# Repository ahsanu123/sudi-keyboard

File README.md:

<p >

</p>

# 🌿 _Sudi_ V2

Sudi V2 is custom wireless split keyboard based on NRF52832 Nordic Semiconductor Microcontroller series, each side consist 18 keys 36 in totals, use MCP23017 I2C 
I/O expansion to scan one side of keyboard, and use wire to trasfer data to NRF52. Built in SWD debug port, with Serial Logger based on CH340G. Sudi Have interactive 
RGB LED and OLED 0.91 inch for graphic display. Planned to create 3D print enclosure.

## 💾 hardware 
hardware is designed with Kicad, you can find out hardware design in `pcb-design` folder. 

**Over simplified workflow**
```mermaid
flowchart TD
    MatrixScanner[Matrix Scanner]
    COR[Chain Of Responsibility]
    FinalReport
    HIDBLEServer[BLE HID Server]

    MatrixScanner --> COR
    COR --> FinalReport
    FinalReport --> HIDBLEServer
```

<details>
  <summary>Casing Design</summary>

</details>

## 🔥 Progress Log

<details>
  <summary>expand this to see current progress 🍰 </summary>

- ~~try to understand why linker script flash ram address need to change from `0x8000` to `0x4000` [look this thread](https://devzone.nordicsemi.com/f/nordic-q-a/78577/nrf-sdk-pre-built-blinky-hex-works-compiled-hex-does-not-nrf51822)~~, use Zephyr instead.
- ~~update hardware readme.md section, add schematic svg~~
- ~~try to logging with segger jlink rtt~~ at 9 september 2024 22:09
- try to logging with serial logger
- ~~add usb to serial (ch340g) if serial logger worked /or considering to use segger rtt (worked and tested on NRF51822)~~
- ~~add on off switch for board~~
- ~~🦀 Change design to use NRF52832~~
- 🔥 Learn more about Zephyr
- ~~change JTAG debugger to component with less space and same pinout based on JLink v8 pinout.~~
- 🔋 ~~battery/and its charger need adjustment, because NRF5232 power supply range is 1.7 V to 3.6 V , and TP4056 will shutdown on 4.2V. if you add AMS1117 3.3v to regulate it, AMS1117 need at least 4.5V to maintain its 3.3V.~~ (NAH, use buck boost instead)
- 🔋 read about BQ24075 bms datasheet
- 🔋 Read about  MAX17048  datasheet
- 🔋 ~~if we use 1.8V for NRF Voltage supply, how its affect other used component~~
  - 🪔 ~~WS2812 VIO level was not satisfied, based on its datasheet, min supply is 3.5, VIH 0.7*VDD (2.45), VIL 0.3 *VDD (1.05)~~
  - ⚗️ ~~based on MCP23017 datashet its power voltage range is 1.8V to 5.5v, VIH 0.25 VDD + 0.8, VIL 0.8 VDD, so its possible to use MCP23017 with 1.8V NRF voltage supply,~~
  - 🐤 ~~CH340G~~
- ~~🔶check 4 pin crystal compatibility~~
- 🦄 ~~change MCU to use NRF52833?? (power supply 1.7-5.5), usb, price +1 dollar 😥, or (NRF52820 only $2.6348)~~
- 🧀 ~~Recheck Silk Screen and componnent~~
- 💸 ~~Create Manufacture id BOM, and Order it~~ about 70 dollar
- 💸 ~~wait dollar until it lower, and order all needed component.~~ shit!!!, dollar does not decline
- ⚽ ~~Final Re-Inspection~~ not doing it actually
- 💸 ~~ordered pcb. 5 Pcs for $15.72 with shipment 7.02 dollar and the pcb is 8.7, still wait for tax. ⏰ 19 januari 2025 at 22:16,~~ arrived in 7 Februari
- 👘 Ordering Component 58 dollar free shipping ( shipping is 7 dollar) , ⏰ 8 Februari 2025
- 💼 Casing - Left Right Connector
- 💼 Casing - top fastener
- 💼 Casing - Battery Holder
- 28 April 2025 ⏰ 05:47, finish one side small component soldering, there is still a lot solder bridge, need to recheck before aplying power
- 🐞 **BUG**, 1 Mei 2025 ⏰17:29, cell pin need to connect into battery pin, not 3.3v

- 🐞 **BUG**, 9 Mei 2025 ⏰ 20:18 current version 2 gerber used for manufacturing pcb is not updated, there is shorted between 3.3v and gnd
- 🐞 **BUG**, 13 Mei 2025 ⏰ 06:52 look and re-calculate inductor 5v buck-boost, when its at full load (all ws28 12 is on) inductor is burn, but ic is not.

> change inductor to use power inductor like VLF4012-2R2 (2.2uH, 1.5A), or choose same capacitance with higher current rate.
>
> look this [lcsc power inductor](https://www.lcsc.com/product-detail/Power-Inductors_MetalLions-MTQH201608S2R2MBT_C17701122.html?s_z=n_VLF4012-2R2%2520)

- 🎰 able to run and flash RMK example with jlink and probe-rs ⏰ 9 Mei 2025, 20:19
- basic setup on WSL, so able to develop in WSL ⏰ 20 Mei 2025, 05:26

  to debugging you need bridge usb device from windows to wsl with `usbipd`

  ```shell
  C:\Windows\System32> usbipd list
  Connected:
  BUSID  VID:PID    DEVICE                                                        STATE
  1-1    feed:0ffa  USB Input Device                                              Not shared
  1-2    0000:3825  USB Input Device                                              Not shared
  1-4    0bda:0129  Realtek USB 2.0 Card Reader                                   Not shared
  1-5    13d3:56cb  USB2.0 HD IR UVC WebCam                                       Not shared
  1-6    1366:0101  J-Link driver                                                 Not shared
  1-10   8087:0026  Intel(R) Wireless Bluetooth(R)                                Not shared

  Persisted:
  GUID                                  DEVICE

  C:\Windows\System32> usbipd bind --busid 1-6

  C:\Windows\System32> usbipd attach --wsl --busid 1-6
  usbipd: info: Using WSL distribution 'Arch' to attach; the device will be available in all WSL 2 distributions.
  usbipd: info: Detected networking mode 'nat'.
  usbipd: info: Using IP address 172.27.144.1 to reach the host.

  C:\Windows\System32>
  ```

  then you can access the usb device as in linux

- 24 Mei 2025, trying to run trouble bas example, its give good sign, even 5v sepic is died for now -> https://github.com/embassy-rs/trouble/blob/main/examples/apps/src/ble_bas_peripheral.rs ⏰ 09:01 

- 25 Mei 2025, able to read uuid for battery level on trouble bas example, also create basic reading uuid with bleak python library, but its really intermitent, bluez is more robust, several note to use and connect bluez with device.

also flashed firmware is from trouble example, current v2 firmware is compiled but not running, 🪞 need to investigate it

```shell
$ bluetoothctl
hci0 new_settings: powered bondable ssp br/edr le secure-conn
Agent registered

[bluetoothctl]> connect FF:E4:05:1A:8F:FF
[bluetoothctl]> disconnect FF:E4:05:1A:8F:FF
[bluetoothctl]> menu gatt
[bluetoothctl]> list-attributes
[bluetoothctl]> select-attribute /org/bluez/hci0/dev_FF_E4_05_1A_8F_FF/service0020/char0021
[bluetoothctl]> read
[bluetoothctl]>
```

- 3 Juli 2025, reading more about trouble, here is `trouble-host-macro` documentation located https://docs.rs/trouble-host-macros/latest/trouble_host_macros/ , here are some note
  - Peripherals may use **GATT** (Generic Attribute Profile) to expose **services** and **characteristics**,
  - still many question about why linker cant linking ble exampl (stack is overflow) even though its identical with example
  - this error ` cannot move location counter backwards (from 3ffdeca8 to 3ffdc000` is because `embassy-executor` `task-arena-<size>` i am not sure why and what value its shouuld be. but without defining task arena its compiled but `panic` on runtime.
  - ok, i find out making `embassy-executor` have `embassy-executor = { version = "0.7.0", features = ["task-arena-size-8192"]}` will make it compiled 😙, need to learn what is that.

finally at ⏰ 21:46 its compiled and able to run, its discoverable with phone 

- 23 Agustus 2025, finally my first SUDI was broke (MCU) and I must finish SUDI v2 for working.
- 24 agustus 2025, basic bas for nrf is compiled and flashed, ⏰ 13:25 

  ⏰ 21:29, able to advertise device as bluetooth hid, but still cant establishing connection to keyboard,
  need to understand how HID keyboard is connected in USB and in BLE.

- 11 September 2025, after reading more about BLE spesification, to more understand what each endpoint / characteristic does in BLE HID, you need to:
  * read characteristic code from [bluetooth assigned number](http://bluetooth.com/wp-content/uploads/Files/Specification/HTML/Assigned_Numbers/out/en/Assigned_Numbers.pdf). for example look at `2a4a` from `hid_info` property in this struct (take from RMK github)
    ```rust
    #[gatt_service(uuid = service::HUMAN_INTERFACE_DEVICE)]
    pub(crate) struct HidService {
        #[characteristic(uuid = "2a4a", read, value = [0x01, 0x01, 0x00, 0x03])]
        pub(crate) hid_info: [u8; 4],
        #[characteristic(uuid = "2a4b", read, value = KeyboardReport::desc().try_into().expect("Failed to convert KeyboardReport to [u8; 67]"))]
        pub(crate) report_map: [u8; 67],
        #[characteristic(uuid = "2a4c", write_without_response)]
        pub(crate) hid_control_point: u8,
        #[characteristic(uuid = "2a4e", read, write_without_response, value = 1)]
        pub(crate) protocol_mode: u8,
        #[descriptor(uuid = "2908", read, value = [0u8, 1u8])]
        #[characteristic(uuid = "2a4d", read, notify)]
        pub(crate) input_keyboard: [u8; 8],
        #[descriptor(uuid = "2908", read, value = [0u8, 2u8])]
        #[characteristic(uuid = "2a4d", read, write, write_without_response)]
        pub(crate) output_keyboard: [u8; 1],
    }
    ```
  * search `2a4a` on BLE Assigned number you will find **HID Information**
    
  * from that information (HID Information), look at [HID over gatt profile](https://www.bluetooth.com/specifications/specs/hid-over-gatt-profile-1-0/)
    
  * it will give you basic information of what is **HID information** is
  * to understand more about what value should provided by your device, you can continue to [Device Class Definition for HID](https://www.usb.org/sites/default/files/hid1_11.pdf), and try to search keyword from _HID over gatt profile_ description, for example `bcountryCode`, search on _Device class definition for HID_ then you will find **HID Descriptor**
    
  * from that information you can conclude `value = [0x01, 0x01, 0x00, 0x03])]` is HID Descriptor, then
  * `0x01` is _bLength_
  * `0x01` is _bDescriptorType_
  * `0x00` is _bcdHID_
  * `0x03` is _bCountryCode_
</details>

## 💳 Reference 

- [RMK - Rust Keyboard Firmware](https://github.com/HaoboGu/rmk/tree/main)   
- [Buck Boost for 3.3v](https://www.eevblog.com/forum/projects/regulating-lipo-battery-to-3-3v/)

<sup>🔥 make it V2 - 19 juni 2024 10:49</sup>

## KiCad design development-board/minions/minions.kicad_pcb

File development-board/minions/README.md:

# Minions

[Assembly View](https://kicanvas.org/?github=https%3A%2F%2Fgithub.com%2Fahsanu123%2Fsudi-keyboard%2Ftree%2Fmain%2Fdevelopment-board%2Fminions)

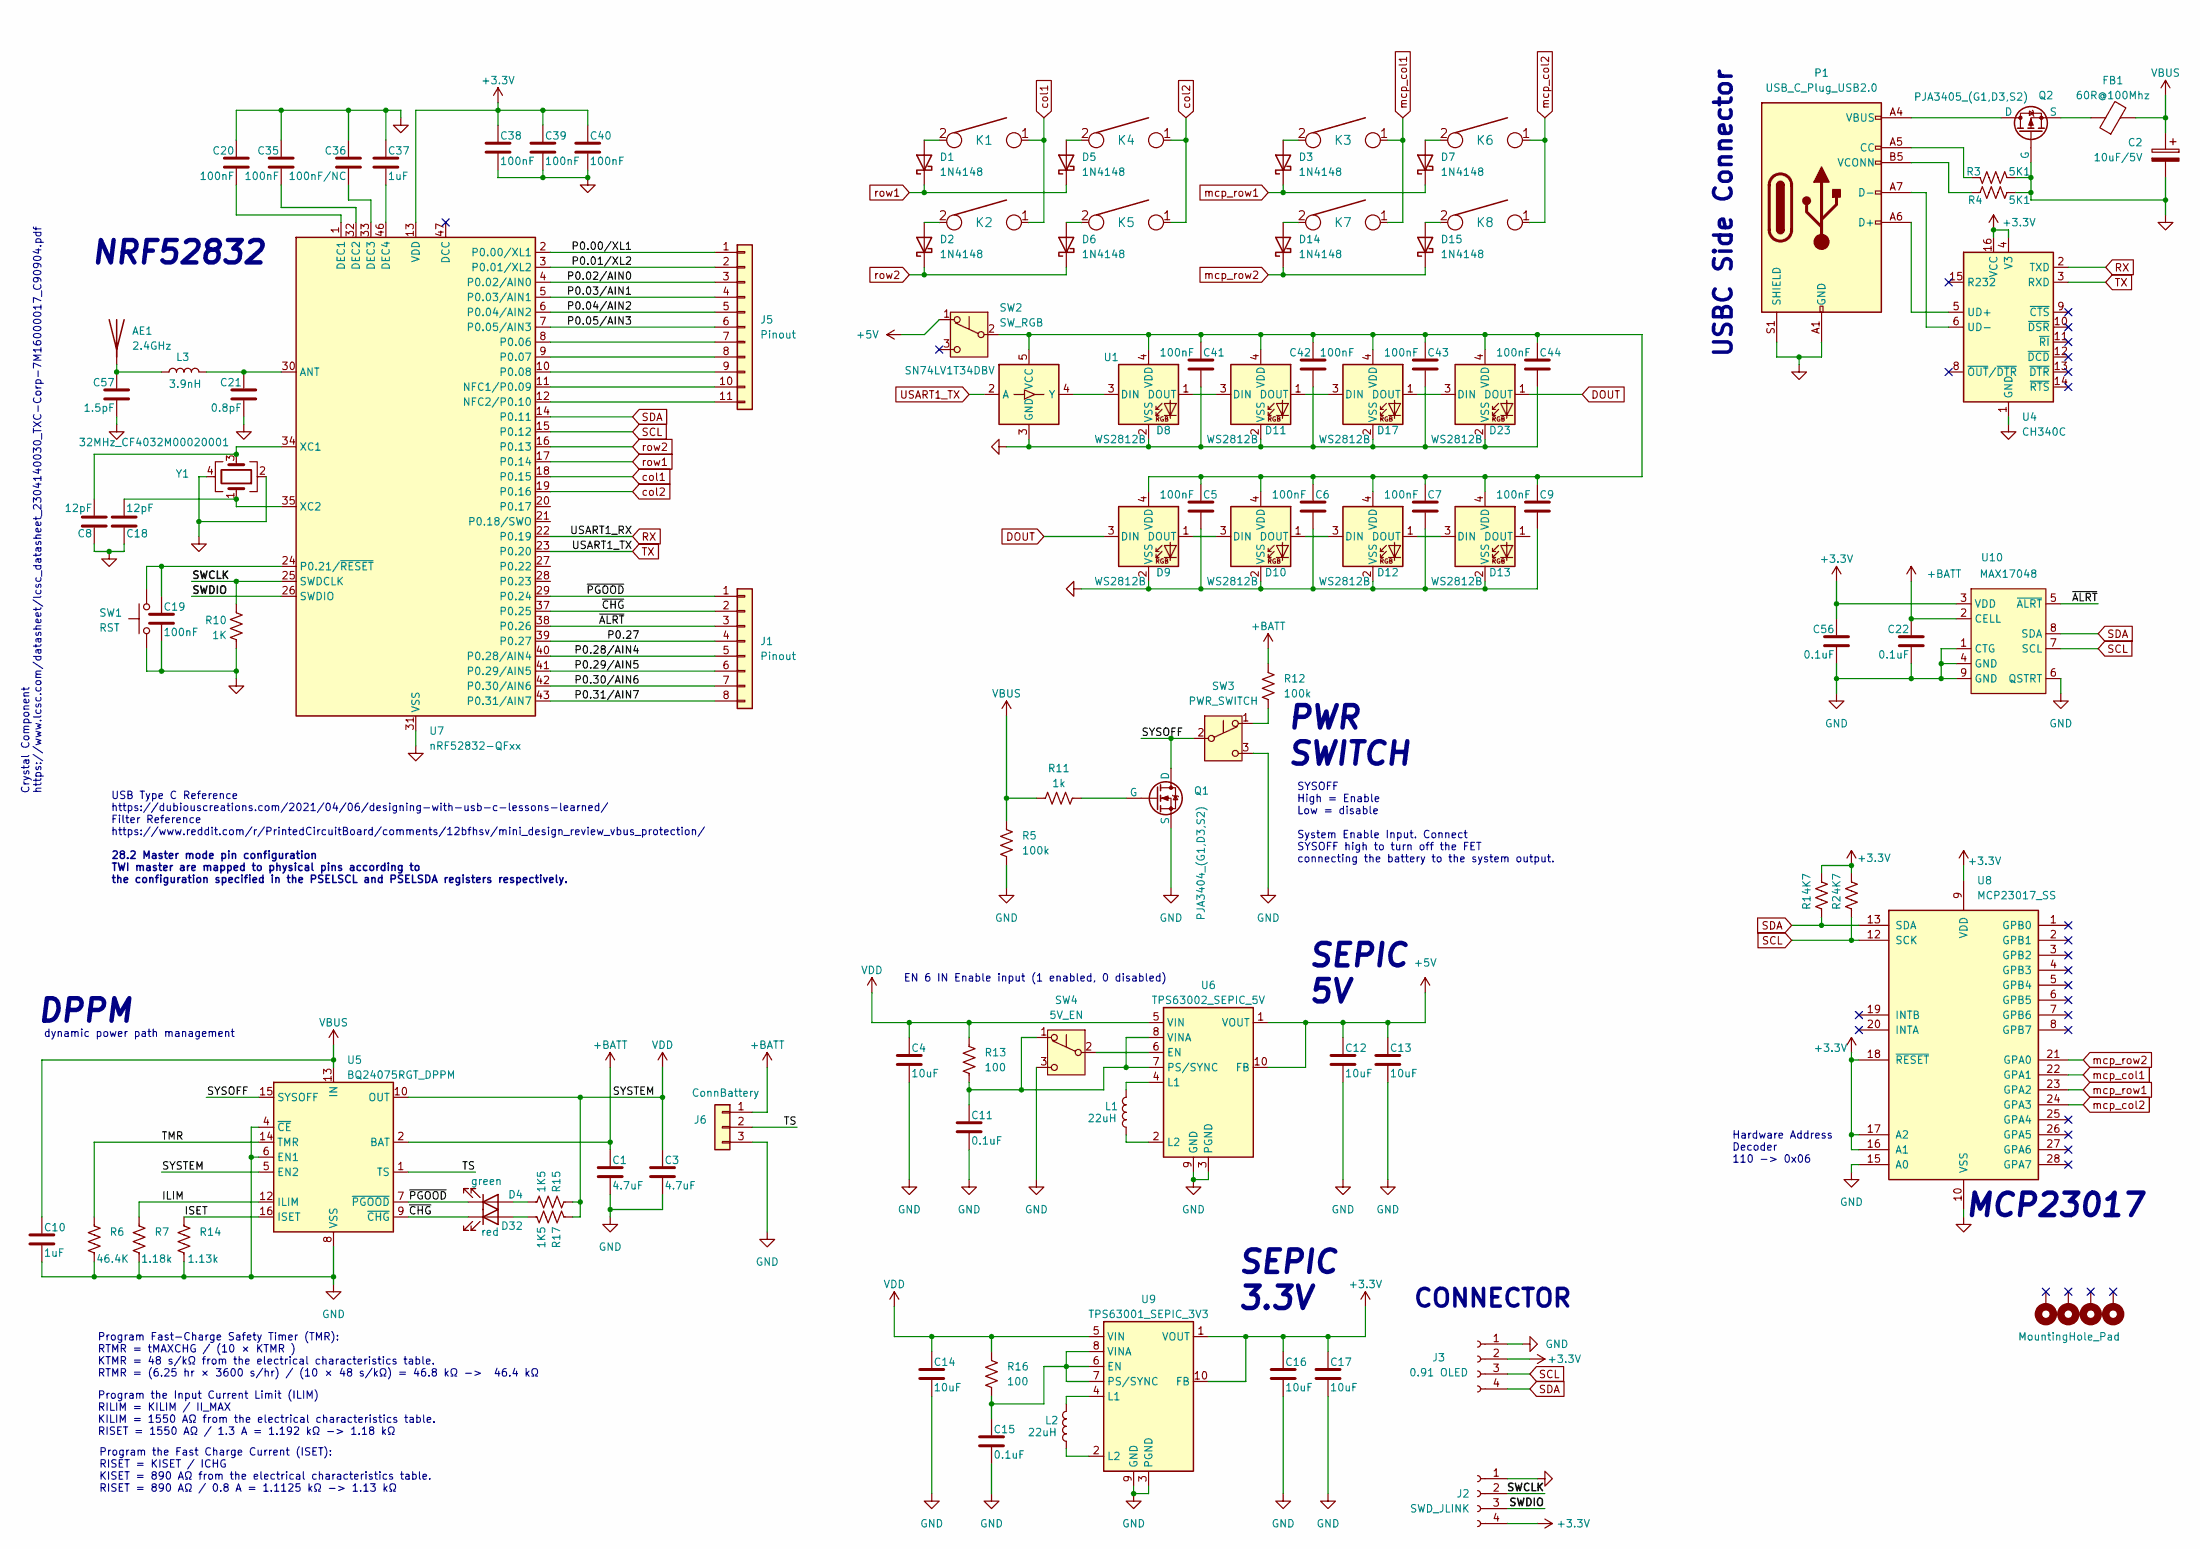
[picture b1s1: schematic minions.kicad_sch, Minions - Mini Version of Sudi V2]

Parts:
AE1: 2.4GHz; Texas_SWRA117D_2.4GHz_Left
C1, C3: 4.7uF; C_0805_2012Metric_Pad1.18x1.45mm_HandSolder
C2: 10uF/5V; C_0805_2012Metric_Pad1.18x1.45mm_HandSolder
C4, C12, C13, C14, C16, C17: 10uF; C_0805_2012Metric_Pad1.18x1.45mm_HandSolder
C5, C6, C7, C9, C19, C20, C35, C38, C39, C40, C41, C42, C43, C44: 100nF; C_0805_2012Metric_Pad1.18x1.45mm_HandSolder
C8, C18: 12pF; C_0805_2012Metric_Pad1.18x1.45mm_HandSolder
C10, C37: 1uF; C_0805_2012Metric_Pad1.18x1.45mm_HandSolder
C11, C15, C22, C56: 0.1uF; C_0805_2012Metric_Pad1.18x1.45mm_HandSolder
C21: 0.8pF; C_0805_2012Metric_Pad1.18x1.45mm_HandSolder
C36: 100nF/NC; C_0805_2012Metric_Pad1.18x1.45mm_HandSolder
C57: 1.5pF; C_0805_2012Metric_Pad1.18x1.45mm_HandSolder
D1, D2, D3, D5, D6, D7, D14, D15: 1N4148; D_SOD123_axial-dual
D4: green; LED_0805_2012Metric_Pad1.15x1.40mm_HandSolder
D8, D9, D10, D11, D12, D13, D17, D23: WS2812B; LED_WS2812B-2020_PLCC4_2.0x2.0mm
D32: red; LED_0805_2012Metric_Pad1.15x1.40mm_HandSolder
FB1: 60R@100Mhz; L_0603_1608Metric_Pad1.05x0.95mm_HandSolder
H4, H5, H6, H7: MountingHole_Pad; MountingHole_3.2mm_M3_DIN965_Pad
J1: Pinout; PinHeader_1x08_P2.54mm_Vertical
J2: SWD_JLINK; PinHeader_1x04_P2.54mm_Vertical
J3: 0.91 OLED; PinHeader_1x04_P2.54mm_Vertical
J5: Pinout; PinHeader_1x11_P2.54mm_Vertical
J6: ConnBattery; PinHeader_1x03_P2.54mm_Vertical
K1, K2, K3, K4, K5, K6, K7, K8: KEYSW; Kailh_socket_MX_optional_reversible_platemount
L1, L2: 22uH; L_Bourns_SRP7028A_7.3x6.6mm
L3: 3.9nH; L_0603_1608Metric_Pad1.05x0.95mm_HandSolder
P1: USB_C_Plug_USB2.0; USB_C_Receptacle_GCT_USB4110
Q1: PJA3404_(G1,D3,S2); SOT-23
Q2: PJA3405_(G1,D3,S2); SOT-23
R1, R2: 4K7; R_0805_2012Metric_Pad1.20x1.40mm_HandSolder
R3, R4: 5K1; R_0805_2012Metric_Pad1.20x1.40mm_HandSolder
R5, R12: 100k; R_0805_2012Metric_Pad1.20x1.40mm_HandSolder
R6: 46.4K; R_0805_2012Metric_Pad1.20x1.40mm_HandSolder
R7: 1.18k; R_0805_2012Metric_Pad1.20x1.40mm_HandSolder
R10: 1K; R_0805_2012Metric_Pad1.20x1.40mm_HandSolder
R11: 1k; R_0805_2012Metric_Pad1.20x1.40mm_HandSolder
R13, R16: 100; R_0805_2012Metric_Pad1.20x1.40mm_HandSolder
R14: 1.13k; R_0805_2012Metric_Pad1.20x1.40mm_HandSolder
R15, R17: 1K5; R_0805_2012Metric_Pad1.20x1.40mm_HandSolder
SW1: RST; SW_Push_1P1T_NO_6x6mm_H9.5mm
SW2: SW_RGB; SW_SPDT_PCM12
SW3: PWR_SWITCH; SW_SPDT_PCM12
SW4: 5V_EN; SW_SPDT_PCM12
U1: SN74LV1T34DBV; SOT-23-5_HandSoldering
U4: CH340C; SOIC-16_3.9x9.9mm_P1.27mm
U5: BQ24075RGT_DPPM; VQFN-16-1EP_3x3mm_P0.5mm_EP1.6x1.6mm
U6: TPS63002_SEPIC_5V; Texas_DRC0010J_ThermalVias
U7: nRF52832-QFxx; QFN-48-1EP_6x6mm_P0.4mm_EP4.6x4.6mm
U8: MCP23017_SS; SSOP-28_5.3x10.2mm_P0.65mm
U9: TPS63001_SEPIC_3V3; Texas_DRC0010J_ThermalVias
U10: MAX17048; DFN-8-1EP_2x2mm_P0.5mm_EP0.8x1.6mm
Y1: 32MHz_CF4032M00020001; Crystal_SMD_3225-4Pin_3.2x2.5mm_HandSoldering

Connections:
+3.3V: C16.1, C17.1, C38.1, C39.1, C40.1, C56.1, J2.4, J3.2, R1.1, R2.1, U4.4 (V3), U4.16 (VCC), U7.13 (VDD), U7.36 (VDD), U7.48 (VDD), U8.9 (VDD), U8.16 (A1), U8.17 (A2), U8.18 (~RESET), U9.1 (VOUT), U9.10 (FB), U10.3 (VDD)
+5V: C12.1, C13.1, SW2.1 (A), U6.1 (VOUT), U6.10 (FB)
+BATT: C1.1, C22.1, J6.1, R12.1, U5.2 (BAT), U5.3 (BAT), U10.2 (CELL)
/ILIM: R7.1, U5.12 (ILIM)
/ISET: R14.1, U5.16 (ISET)
/P0.00/XL1: J5.1, U7.2 (P0.00/XL1)
/P0.01/XL2: J5.2, U7.3 (P0.01/XL2)
/P0.02/AIN0: J5.3, U7.4 (P0.02/AIN0)
/P0.03/AIN1: J5.4, U7.5 (P0.03/AIN1)
/P0.04/AIN2: J5.5, U7.6 (P0.04/AIN2)
/P0.05/AIN3: J5.6, U7.7 (P0.05/AIN3)
/P0.27: J1.4, U7.39 (P0.27)
/P0.28/AIN4: J1.5, U7.40 (P0.28/AIN4)
/P0.29/AIN5: J1.6, U7.41 (P0.29/AIN5)
/P0.30/AIN6: J1.7, U7.42 (P0.30/AIN6)
/P0.31/AIN7: J1.8, U7.43 (P0.31/AIN7)
/SWCLK: J2.2, R10.2, U7.25 (SWDCLK)
/SWDIO: J2.3, U7.26 (SWDIO)
/SYSOFF: Q1.3 (D), SW3.2 (B), U5.15 (SYSOFF)
/TMR: R6.1, U5.14 (TMR)
/TS: J6.2, U5.1 (TS)
/~ALRT: J1.3, U7.38 (P0.26), U10.5 (~ALRT)
/~CHG: D32.1 (K), J1.2, U5.9 (~CHG), U7.37 (P0.25)
/~PGOOD: D4.1 (K), J1.1, U5.7 (~PGOOD), U7.29 (P0.24)
DOUT: D9.3 (DIN), D23.1 (DOUT)
GND: C1.2, C2.2, C3.2, C4.2, C5.2, C6.2, C7.2, C8.1, C9.2, C10.2, C11.2, C12.2, C13.2, C14.2, C15.2, C16.2, C17.2, C18.1, C19.2, C20.1, C21.2, C22.2, C35.1, C36.1, C37.1, C38.2, C39.2, C40.2, C41.2, C42.2, C43.2, C44.2, C56.2, C57.2, D8.2 (VSS), D9.2 (VSS), D10.2 (VSS), D11.2 (VSS), D12.2 (VSS), D13.2 (VSS), D17.2 (VSS), D23.2 (VSS), J2.1, J3.1, J6.3, P1.A1 (GND), P1.A12 (GND), P1.B1 (GND), P1.B12 (GND), P1.S1 (SHIELD), Q1.2 (S), Q2.1 (G), R3.2, R4.2, R5.2, R6.2, R7.2, R10.1, R14.2, SW1.1, SW3.3 (C), SW4.3 (C), U1.3 (GND), U4.1 (GND), U5.4 (~CE), U5.6 (EN1), U5.8 (VSS), U5.17 (VSS), U6.3 (PGND), U6.9 (GND), U6.11 (PGND), U7.31 (VSS), U7.45 (VSS), U7.49 (VSS), U8.10 (VSS), U8.15 (A0), U9.3 (PGND), U9.9 (GND), U9.11 (PGND), U10.1 (CTG), U10.4 (GND), U10.6 (QSTRT), U10.9 (GND), Y1.2, Y1.4
unnamed: AE1.1 (A), C57.1, L3.1
unnamed: D1.2 (A), K1.2
unnamed: D2.2 (A), K2.2
unnamed: D3.2 (A), K3.2
unnamed: D4.2 (A), R15.1
unnamed: D5.2 (A), K4.2
unnamed: D6.2 (A), K5.2
unnamed: D7.2 (A), K6.2
unnamed: D8.3 (DIN), U1.4 (Y)
unnamed: D9.1 (DOUT), D10.3 (DIN)
unnamed: D10.1 (DOUT), D12.3 (DIN)
unnamed: C5.1, C6.1, C7.1, C9.1, C41.1, C42.1, C43.1, C44.1, D8.4 (VDD), D9.4 (VDD), D10.4 (VDD), D11.4 (VDD), D12.4 (VDD), D13.4 (VDD), D17.4 (VDD), D23.4 (VDD), SW2.2 (B), U1.5 (VCC)
unnamed: D8.1 (DOUT), D11.3 (DIN)
unnamed: D11.1 (DOUT), D17.3 (DIN)
unnamed: D12.1 (DOUT), D13.3 (DIN)
unnamed: D14.2 (A), K7.2
unnamed: D15.2 (A), K8.2
unnamed: D17.1 (DOUT), D23.3 (DIN)
unnamed: D32.2 (A), R17.1
unnamed: J5.7, U7.8 (P0.06)
unnamed: J5.8, U7.9 (P0.07)
unnamed: J5.9, U7.10 (P0.08)
unnamed: J5.10, U7.11 (NFC1/P0.09)
unnamed: J5.11, U7.12 (NFC2/P0.10)
unnamed: P1.A5 (CC), R3.1
unnamed: P1.A6 (D+), U4.5 (UD+)
unnamed: P1.A7 (D-), U4.6 (UD-)
unnamed: P1.B5 (VCONN), R4.1
unnamed: Q1.1 (G), R11.2
unnamed: P1.A4 (VBUS), P1.A9 (VBUS), P1.B4 (VBUS), P1.B9 (VBUS), Q2.3 (D)
unnamed: FB1.1, Q2.2 (S)
unnamed: R12.2, SW3.1 (A)
unnamed: C11.1, R13.2, SW4.1 (A), U6.7 (PS/SYNC), U6.8 (VINA)
unnamed: SW4.2 (B), U6.6 (EN)
unnamed: L1.2, U6.4 (L1)
unnamed: L1.1, U6.2 (L2)
unnamed: C21.1, L3.2, U7.30 (ANT)
unnamed: C20.2, U7.1 (DEC1)
unnamed: C35.2, U7.32 (DEC2)
unnamed: C36.2, U7.33 (DEC3)
unnamed: C37.2, U7.46 (DEC4)
unnamed: C19.1, SW1.2, U7.24 (P0.21/~RESET)
unnamed: C8.2, U7.34 (XC1), Y1.3
unnamed: C18.2, U7.35 (XC2), Y1.1
unnamed: C15.1, R16.2, U9.6 (EN), U9.7 (PS/SYNC), U9.8 (VINA)
unnamed: L2.2, U9.4 (L1)
unnamed: L2.1, U9.2 (L2)
RX: U4.2 (TXD), U7.22 (P0.19)
SCL: J3.3, R2.2, U7.15 (P0.12), U8.12 (SCK), U10.7 (SCL)
SDA: J3.4, R1.2, U7.14 (P0.11), U8.13 (SDA), U10.8 (SDA)
TX: U1.2 (A), U4.3 (RXD), U7.23 (P0.20)
VBUS: C2.1, C10.1, FB1.2, R5.1, R11.1, U5.13 (IN)
VDD: C3.1, C4.1, C14.1, R13.1, R15.2, R16.1, R17.2, U5.5 (EN2), U5.10 (OUT), U5.11 (OUT), U6.5 (VIN), U9.5 (VIN)
col1: K1.1, K2.1, U7.18 (P0.15)
col2: K4.1, K5.1, U7.19 (P0.16)
mcp_col1: K3.1, K7.1, U8.22 (GPA1)
mcp_col2: K6.1, K8.1, U8.24 (GPA3)
mcp_row1: D3.1 (K), D7.1 (K), U8.23 (GPA2)
mcp_row2: D14.1 (K), D15.1 (K), U8.21 (GPA0)
row1: D1.1 (K), D5.1 (K), U7.17 (P0.14)
row2: D2.1 (K), D6.1 (K), U7.16 (P0.13)

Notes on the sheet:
DPPM
EN 6 IN Enable input (1 enabled, 0 disabled)
dynamic power path management
28.2 Master mode pin configuration TWI master are mapped to physical pins according to the configuration specified in the PSELSCL and PSELSDA registers respectively.
SEPIC 5V
USB Type C Reference https://dubiouscreations.com/2021/04/06/designing-with-usb-c-lessons-learned/ Filter Reference https://www.reddit.com/r/PrintedCircuitBoard/comments/12bfhsv/mini_design_review_vbus_protection/
Program the Input Current Limit (ILIM) RILIM = KILIM / II_MAX KILIM = 1550 AΩ from the electrical characteristics table. RISET = 1550 AΩ / 1.3 A = 1.192 kΩ -> 1.18 kΩ
USBC Side Connector
NRF52832
MCP23017
PWR SWITCH
SEPIC 3.3V
Crystal Component https://www.lcsc.com/datasheet/lcsc_datasheet_2304140030_TXC-Corp-7M16000017_C90904.pdf
Program the Fast Charge Current (ISET): RISET = KISET / ICHG KISET = 890 AΩ from the electrical characteristics table. RISET = 890 AΩ / 0.8 A = 1.1125 kΩ -> 1.13 kΩ
CONNECTOR
Hardware Address Decoder 110 -> 0x06
Program Fast-Charge Safety Timer (TMR): RTMR = tMAXCHG / (10 × KTMR ) KTMR = 48 s/kΩ from the electrical characteristics table. RTMR = (6.25 hr × 3600 s/hr) / (10 × 48 s/kΩ) = 46.8 kΩ -> 46.4 kΩ
SYSOFF High = Enable Low = disable System Enable Input. Connect SYSOFF high to turn off the FET connecting the battery to the system output.

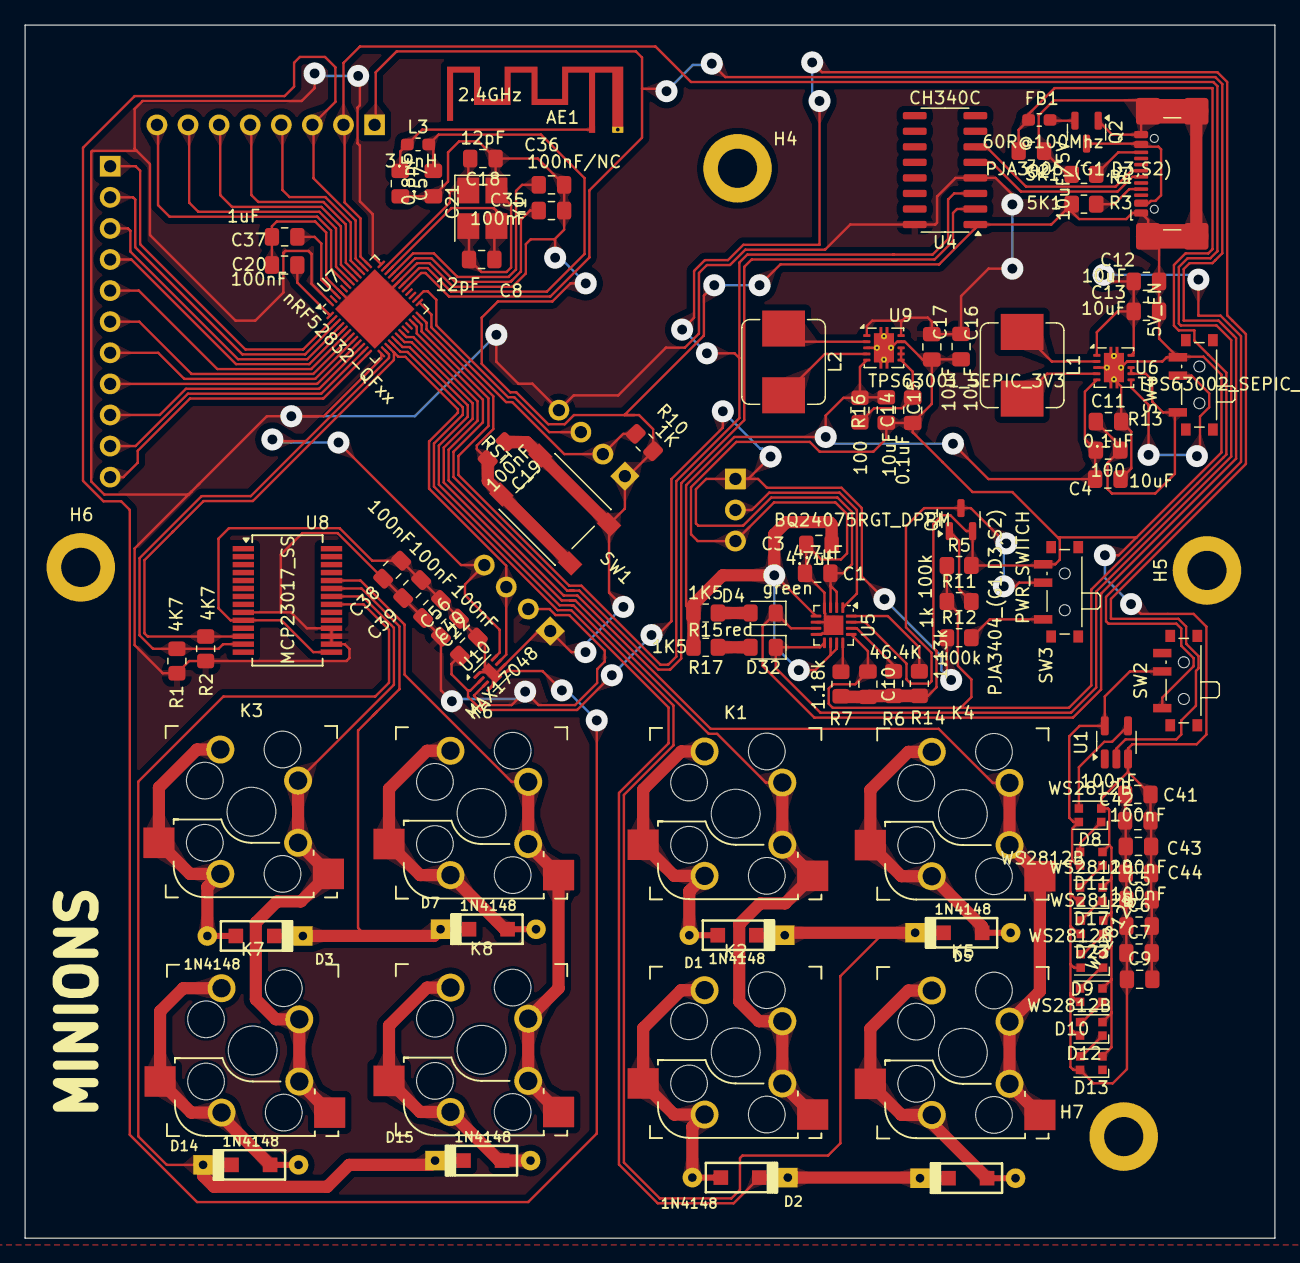
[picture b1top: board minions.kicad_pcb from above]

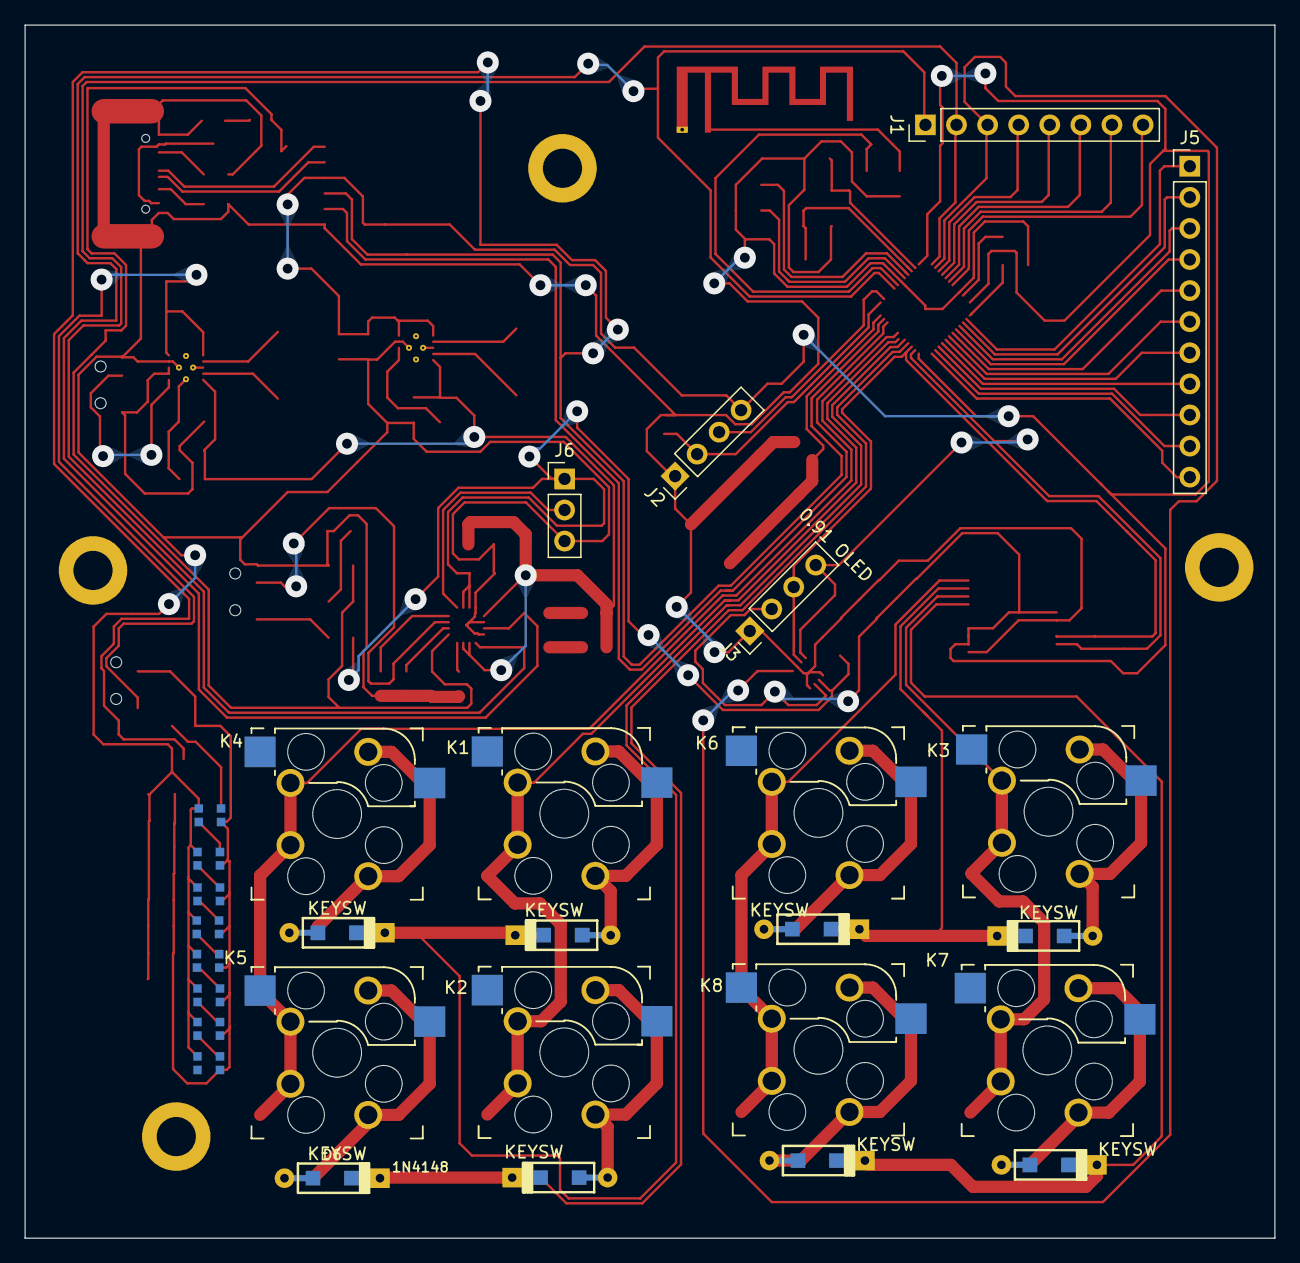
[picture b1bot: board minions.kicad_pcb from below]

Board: 2 copper layers, 102.1 x 99.1 mm, 105 parts (14 on the bottom side), 87 nets.

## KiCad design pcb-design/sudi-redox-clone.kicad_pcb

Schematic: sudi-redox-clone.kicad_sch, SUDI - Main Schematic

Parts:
AE1: 2.4GHz; Texas_SWRA117D_2.4GHz_Left
C1, C4: 10uF; C_0805_2012Metric_Pad1.18x1.45mm_HandSolder
C2, C3: 10uF/5V; C_0805_2012Metric_Pad1.18x1.45mm_HandSolder
C11, C13, C21: 100nF; C_0805_2012Metric_Pad1.18x1.45mm_HandSolder
C12: 47nF; C_0805_2012Metric_Pad1.18x1.45mm_HandSolder
C14: 1nF; C_0805_2012Metric_Pad1.18x1.45mm_HandSolder
C15: 2.2pF; C_0805_2012Metric_Pad1.18x1.45mm_HandSolder
C16: 1pF; C_0805_2012Metric_Pad1.18x1.45mm_HandSolder
C17: 1.5p; C_0805_2012Metric_Pad1.18x1.45mm_HandSolder
C18: 2.2nF; C_0805_2012Metric_Pad1.18x1.45mm_HandSolder
C19, C20: 12pF; C_0805_2012Metric_Pad1.18x1.45mm_HandSolder
D1, D2, D3, D7, D8, D9, D13, D14, D15, D19, D20, D21, D25, D26, D27, D29, D30, D31: 1N5820; D_SOD123_axial-dual
D4: RED; LED_0805_2012Metric_Pad1.15x1.40mm_HandSolder
D5, D6, D10, D11, D12, D16, D17, D18, D22, D23, D24, D28, D43, D44, D45, D46, D47, D48: WS2812B; LED_WS2812B_PLCC4_5.0x5.0mm_P3.2mm
FB1: 60R@100Mhz; L_0603_1608Metric_Pad1.05x0.95mm_HandSolder
FID1, FID2, FID3, FID4, FID5, FID6, FID7, FID8, FID9: Fiducial; Fiducial_1mm_Mask3mm
H1, H2, H3, H4, H5, H6, H7, H8, H9: MountingHole_Pad; MountingHole_3.2mm_M3_DIN965_Pad
J1: RJ12_LEFT; RJ25_Wayconn_MJEA-660X1_Horizontal
J2: 0.91 OLED; PinHeader_1x04_P2.54mm_Vertical
J3: RJ12_RIGHT; RJ25_Wayconn_MJEA-660X1_Horizontal
J4: USBC_PWR_ONLY; USB_C_Receptacle_GCT_USB4125-xx-x-0190_6P_TopMnt_Horizontal
J7: ARMJTAG; PinHeader_2x05_P2.54mm_Horizontal
J8: BatCon; PinHeader_1x02_P2.54mm_Horizontal
K1, K2, K3, K4, K5, K6, K7, K8, K9, K10, K11, K12, K13, K14, K15, K16, K17, K18: KEYSW; Mx_Alps_100-dualside
L1: 10nH; L_0603_1608Metric_Pad1.05x0.95mm_HandSolder
L2: 4.7nH; L_0603_1608Metric_Pad1.05x0.95mm_HandSolder
L3: 3.3nH; L_0603_1608Metric_Pad1.05x0.95mm_HandSolder
R1, R2: 4K7; R_1206_3216Metric
R3, R4: 5K1; R_1206_3216Metric
R5, R6: 1K; R_1206_3216Metric
R7: 1.2; R_1206_3216Metric
U4: AMS1117-3.3; SOT-223-3_TabPin2
U5: nRF51x22-QFxx; QFN-48-1EP_6x6mm_P0.4mm_EP4.6x4.6mm
U6: TP4056; SOIC-8-1EP_3.9x4.9mm_P1.27mm_EP2.29x3mm
U8: MCP23017_SS; SSOP-28_5.3x10.2mm_P0.65mm
Y2: 16MHz; Crystal_HC50_Vertical

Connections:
+3.3V: C3.1, C13.1, C14.1, C21.1, J7.1 (VTref), R1.1, R2.1, U4.2 (VO), U5.1 (VDD), U5.12 (VDD), U5.35 (AVDD), U5.36 (AVDD), U8.9 (VDD); also elsewhere on the board
+3V7: D5.1 (VDD), D6.1 (VDD), D10.1 (VDD), D11.1 (VDD), D12.1 (VDD), D16.1 (VDD), D17.1 (VDD), D18.1 (VDD), D22.1 (VDD), D23.1 (VDD), D24.1 (VDD), D28.1 (VDD), D43.1 (VDD), D44.1 (VDD), D45.1 (VDD), D46.1 (VDD), D47.1 (VDD), D48.1 (VDD), J1.5, J2.2, J3.5
+5V: C1.1, C2.1, D4.2 (A), FB1.2, J1.6, J3.6, U4.3 (VI), U6.4 (VCC), U6.8 (CE), U8.16 (A1), U8.17 (A2), U8.18 (~RESET); also elsewhere on the board
/I2C2_SCL: U5.4 (P0.0)
/I2C2_SDA: U5.5 (P0.1)
/SWCLK: J7.4 (SWCLK/TCK), R5.2, U5.24 (SWDCLK)
/SWDIO: J7.2 (SWDIO/TMS), U5.23 (SWDIO/~RST)
/USART1_RX: U5.7 (P0.3)
/USART1_TX: D43.4 (DIN), U5.6 (P0.2)
GND: C1.2, C2.2, C3.2, C4.2, C11.2, C12.2, C13.2, C14.2, C16.2, C17.2, C18.2, C19.1, C20.1, C21.2, D5.3 (VSS), D6.3 (VSS), D10.3 (VSS), D11.3 (VSS), D12.3 (VSS), D16.3 (VSS), D17.3 (VSS), D18.3 (VSS), D22.3 (VSS), D23.3 (VSS), D24.3 (VSS), D28.3 (VSS), D43.3 (VSS), D44.3 (VSS), D45.3 (VSS), D46.3 (VSS), D47.3 (VSS), D48.3 (VSS), H8.1, H9.1, J1.1, J2.1, J3.1, J4.A12 (GND), J4.B12 (GND), J4.S1 (SHIELD), J7.3 (GND), J7.5 (GND), J7.9 (GNDDetect), J8.2, R3.2, R4.2, R5.1, R7.1, U4.1 (GND), U5.13 (VSS), U5.33 (VSS), U5.34 (VSS), U5.49 (EP), U6.3 (GND), U8.10 (VSS), U8.15 (A0); also elsewhere on the board
unnamed: AE1.1 (A), C17.1, L3.1
unnamed: C15.2, C16.1, L3.2
unnamed: D1.2 (A), K1.2
unnamed: D2.2 (A), K2.2
unnamed: D3.2 (A), K3.2
unnamed: D4.1 (K), R6.2
unnamed: D5.2 (DOUT), D6.4 (DIN)
unnamed: D7.2 (A), K4.2
unnamed: D8.2 (A), K5.2
unnamed: D9.2 (A), K6.2
unnamed: D6.2 (DOUT), D10.4 (DIN)
unnamed: D10.2 (DOUT), D11.4 (DIN)
unnamed: D11.2 (DOUT), D12.4 (DIN)
unnamed: D12.2 (DOUT), D16.4 (DIN)
unnamed: D13.2 (A), K7.2
unnamed: D14.2 (A), K8.2
unnamed: D15.2 (A), K9.2
unnamed: D16.2 (DOUT), D17.4 (DIN)
unnamed: D17.2 (DOUT), D18.4 (DIN)
unnamed: D18.2 (DOUT), D22.4 (DIN)
unnamed: D19.2 (A), K10.2
unnamed: D20.2 (A), K11.2
unnamed: D21.2 (A), K12.2
unnamed: D22.2 (DOUT), D23.4 (DIN)
unnamed: D23.2 (DOUT), D24.4 (DIN)
unnamed: D24.2 (DOUT), D28.4 (DIN)
unnamed: D25.2 (A), K13.2
unnamed: D26.2 (A), K14.2
unnamed: D27.2 (A), K15.2
unnamed: D29.2 (A), K16.2
unnamed: D30.2 (A), K17.2
unnamed: D31.2 (A), K18.2
unnamed: D43.2 (DOUT), D44.4 (DIN)
unnamed: D44.2 (DOUT), D45.4 (DIN)
unnamed: D45.2 (DOUT), D46.4 (DIN)
unnamed: D46.2 (DOUT), D47.4 (DIN)
unnamed: D47.2 (DOUT), D48.4 (DIN)
unnamed: D5.4 (DIN), D48.2 (DOUT)
unnamed: FB1.1, J4.A9 (VBUS), J4.B9 (VBUS)
unnamed: J4.A5 (CC1), R3.1
unnamed: J4.B5 (CC2), R4.1
unnamed: C4.1, J8.1, U6.5 (BAT)
unnamed: L1.1, L2.2, U5.31 (ANT1)
unnamed: C15.1, L2.1, U5.32 (ANT2)
unnamed: C11.1, U5.39 (DEC1)
unnamed: C12.1, U5.29 (DEC2)
unnamed: C18.1, L1.2, U5.30 (VDD_PA)
unnamed: C19.2, U5.37 (XC1), Y2.1
unnamed: C20.2, U5.38 (XC2), Y2.2
unnamed: R7.2, U6.2 (PROG)
unnamed: R6.1, U6.7 (~CHRG)
SCL: J1.3, J2.3, J3.3, R2.2, U8.12 (SCK)
SDA: J1.4, J2.4, J3.4, R1.2, U8.13 (SDA)
Tx: J1.2, J3.2
col1: K1.1, K2.1, K3.1, U5.11 (P0.7), U8.1 (GPB0)
col2: K4.1, K5.1, K6.1, U5.14 (P0.8), U8.2 (GPB1)
col3: K7.1, K8.1, K9.1, U5.15 (P0.9), U8.3 (GPB2)
col4: K10.1, K11.1, K12.1, U5.16 (P0.10), U8.4 (GPB3)
col5: K13.1, K14.1, K15.1, U5.17 (P0.11), U8.5 (GPB4)
col6: K16.1, K17.1, K18.1, U5.18 (P0.12), U8.6 (GPB5)
row1: D1.1 (K), D7.1 (K), D13.1 (K), D19.1 (K), D25.1 (K), D29.1 (K), U5.8 (P0.4), U8.21 (GPA0)
row2: D2.1 (K), D8.1 (K), D14.1 (K), D20.1 (K), D26.1 (K), D30.1 (K), U5.9 (P0.5), U8.22 (GPA1)
row3: D3.1 (K), D9.1 (K), D15.1 (K), D21.1 (K), D27.1 (K), D31.1 (K), U5.10 (P0.6), U8.23 (GPA2)

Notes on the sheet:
SUDI - Split Keyboard SUDI is my custom split keyboard based on redox, it will designed with 75%+ keyboard layout (84 key with 42 each side). use promicro for main MCU and MCP23017 for 16bit bidirectional I/O expantion kailh hot swap
OLED 0.91'
28.2 Master mode pin configuration TWI master are mapped to physical pins according to the configuration specified in the PSELSCL and PSELSDA registers respectively.
V2 TODO make it wireless with NRF51822 add BMS to System (TP4056) make receiver and transmitter with NRF use LUFA with ATMega8 for usb receiver / RECEIVER SCH https://www.fourwalledcubicle.com/files/LUFA/Doc/120219/html/_page__a_v_r8_support.html https://developer.nordicsemi.com/nRF5_SDK/nRF51_SDK_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
NOTE: Used Real Diode 1N4148
Key Matrix
USB Type C Reference https://dubiouscreations.com/2021/04/06/designing-with-usb-c-lessons-learned/ Filter Reference https://www.reddit.com/r/PrintedCircuitBoard/comments/12bfhsv/mini_design_review_vbus_protection/
Hardware Address Decoder 110 -> 0x06
ADD USB B Backup
RJ12 Female Conn Change To Correct Footprint
Ref: Figure 24 NRF51822 Datasheet
MCP23017

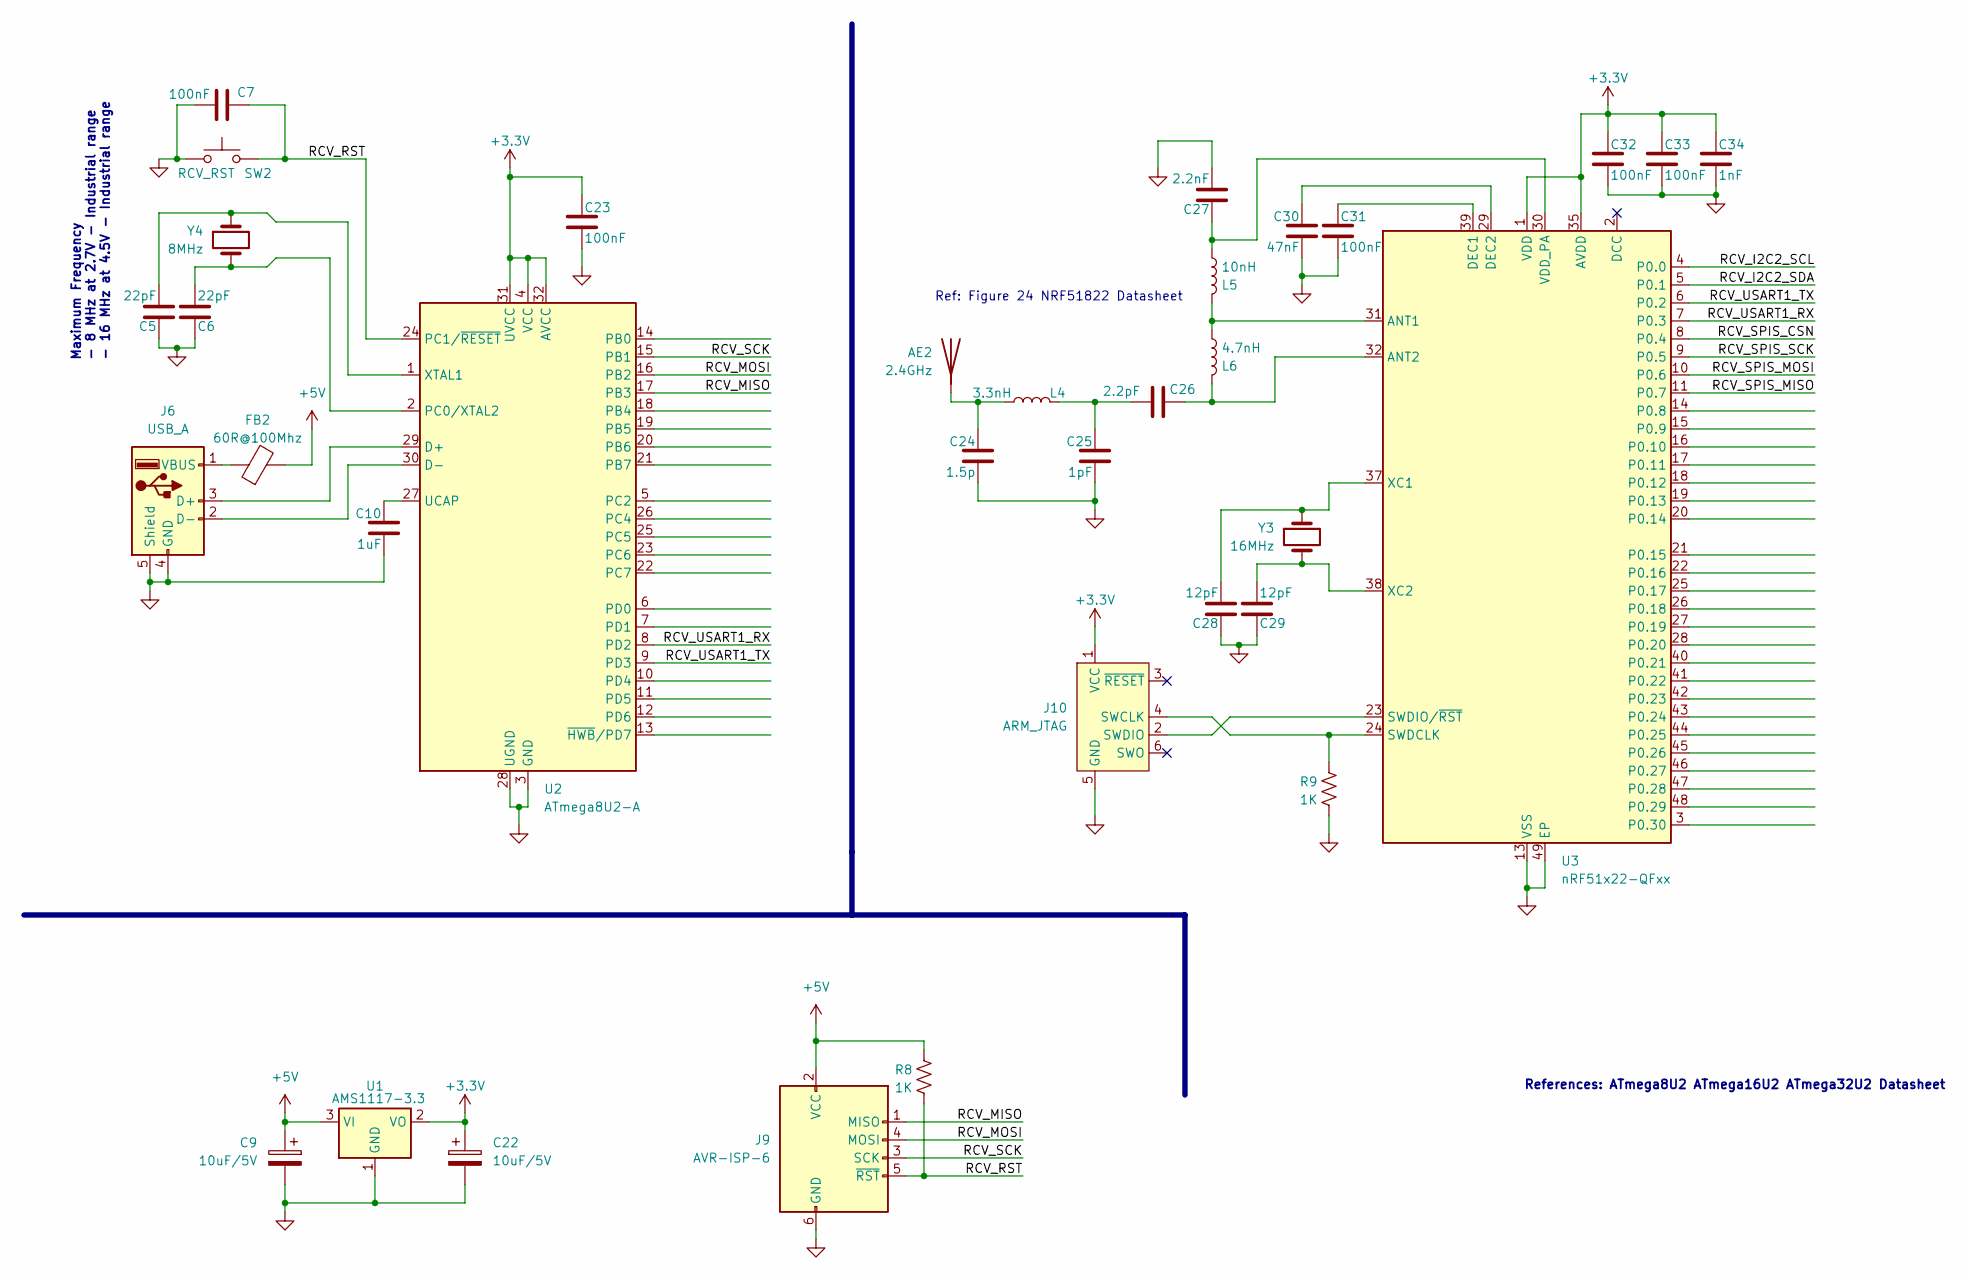
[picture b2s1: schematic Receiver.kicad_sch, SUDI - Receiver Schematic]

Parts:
AE2: 2.4GHz; Texas_SWRA117D_2.4GHz_Left
C5, C6: 22pF; C_0805_2012Metric_Pad1.18x1.45mm_HandSolder
C7, C23, C31, C32, C33: 100nF; C_0805_2012Metric_Pad1.18x1.45mm_HandSolder
C9, C22: 10uF/5V; C_0805_2012Metric_Pad1.18x1.45mm_HandSolder
C10: 1uF; C_0805_2012Metric_Pad1.18x1.45mm_HandSolder
C24: 1.5p; C_0805_2012Metric_Pad1.18x1.45mm_HandSolder
C25: 1pF; C_0805_2012Metric_Pad1.18x1.45mm_HandSolder
C26: 2.2pF; C_0805_2012Metric_Pad1.18x1.45mm_HandSolder
C27: 2.2nF; C_0805_2012Metric_Pad1.18x1.45mm_HandSolder
C28, C29: 12pF; C_0805_2012Metric_Pad1.18x1.45mm_HandSolder
C30: 47nF; C_0805_2012Metric_Pad1.18x1.45mm_HandSolder
C34: 1nF; C_0805_2012Metric_Pad1.18x1.45mm_HandSolder
FB2: 60R@100Mhz; L_0603_1608Metric_Pad1.05x0.95mm_HandSolder
J6: USB_A; USB_A_CNCTech_1001-011-01101_Horizontal
J9: AVR-ISP-6; PinHeader_2x05_P2.54mm_Vertical
J10: ARM_JTAG; PinHeader_2x05_P1.27mm_Vertical
L4: 3.3nH; L_0603_1608Metric_Pad1.05x0.95mm_HandSolder
L5: 10nH; L_0603_1608Metric_Pad1.05x0.95mm_HandSolder
L6: 4.7nH; L_0603_1608Metric_Pad1.05x0.95mm_HandSolder
R8, R9: 1K; R_1206_3216Metric
SW2: RCV_RST; SW_Push_1P1T_NO_6x6mm_H9.5mm
U1: AMS1117-3.3; SOT-223-3_TabPin2
U2: ATmega8U2-A; TQFP-32_7x7mm_P0.8mm
U3: nRF51x22-QFxx; QFN-48-1EP_6x6mm_P0.4mm_EP4.6x4.6mm
Y3: 16MHz; Crystal_HC50_Vertical
Y4: 8MHz; Crystal_HC50_Vertical

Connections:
+3.3V: C22.1, C23.1, C32.1, C33.1, C34.1, J10.1 (VCC), U1.2 (VO), U2.4 (VCC), U2.31 (UVCC), U2.32 (AVCC), U3.1 (VDD), U3.12 (VDD), U3.35 (AVDD), U3.36 (AVDD); also elsewhere on the board
+5V: C9.1, FB2.2, J9.2 (VCC), R8.2, U1.3 (VI); also elsewhere on the board
/Receiver/RCV_I2C2_SCL: U3.4 (P0.0)
/Receiver/RCV_I2C2_SDA: U3.5 (P0.1)
/Receiver/RCV_MISO: J9.1 (MISO), U2.17 (PB3)
/Receiver/RCV_MOSI: J9.4 (MOSI), U2.16 (PB2)
/Receiver/RCV_RST: C7.1, J9.5 (~RST), R8.1, SW2.2, U2.24 (PC1/~RESET)
/Receiver/RCV_SCK: J9.3 (SCK), U2.15 (PB1)
/Receiver/RCV_SPIS_CSN: U3.8 (P0.4)
/Receiver/RCV_SPIS_MISO: U3.11 (P0.7)
/Receiver/RCV_SPIS_MOSI: U3.10 (P0.6)
/Receiver/RCV_SPIS_SCK: U3.9 (P0.5)
/Receiver/RCV_USART1_RX: U2.8 (PD2), U3.7 (P0.3)
/Receiver/RCV_USART1_TX: U2.9 (PD3), U3.6 (P0.2)
GND: C5.1, C6.1, C7.2, C9.2, C10.2, C22.2, C23.2, C24.2, C25.2, C27.2, C28.1, C29.1, C30.2, C31.2, C32.2, C33.2, C34.2, J6.4 (GND), J6.5 (Shield), J9.6 (GND), J10.5 (GND), R9.1, SW2.1, U1.1 (GND), U2.3 (GND), U2.28 (UGND), U3.13 (VSS), U3.33 (VSS), U3.34 (VSS), U3.49 (EP); also elsewhere on the board
unnamed: AE2.1 (A), C24.1, L4.1
unnamed: C25.1, C26.2, L4.2
unnamed: J6.3 (D+), U2.29 (D+)
unnamed: J6.2 (D-), U2.30 (D-)
unnamed: FB2.1, J6.1 (VBUS)
unnamed: J10.4 (SWCLK), R9.2, U3.24 (SWDCLK)
unnamed: J10.2 (SWDIO), U3.23 (SWDIO/~RST)
unnamed: C6.2, U2.2 (PC0/XTAL2), Y4.2
unnamed: C10.1, U2.27 (UCAP)
unnamed: C5.2, U2.1 (XTAL1), Y4.1
unnamed: L5.1, L6.2, U3.31 (ANT1)
unnamed: C26.1, L6.1, U3.32 (ANT2)
unnamed: C31.1, U3.39 (DEC1)
unnamed: C30.1, U3.29 (DEC2)
unnamed: C27.1, L5.2, U3.30 (VDD_PA)
unnamed: C28.2, U3.37 (XC1), Y3.1
unnamed: C29.2, U3.38 (XC2), Y3.2

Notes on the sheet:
Maximum Frequency - 8 MHz at 2.7V - Industrial range - 16 MHz at 4.5V - Industrial range
Ref: Figure 24 NRF51822 Datasheet
References: ATmega8U2 ATmega16U2 ATmega32U2 Datasheet
